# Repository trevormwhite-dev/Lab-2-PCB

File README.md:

# Suggested Changes on Issues Tab
# Check them off if/when they are fixed

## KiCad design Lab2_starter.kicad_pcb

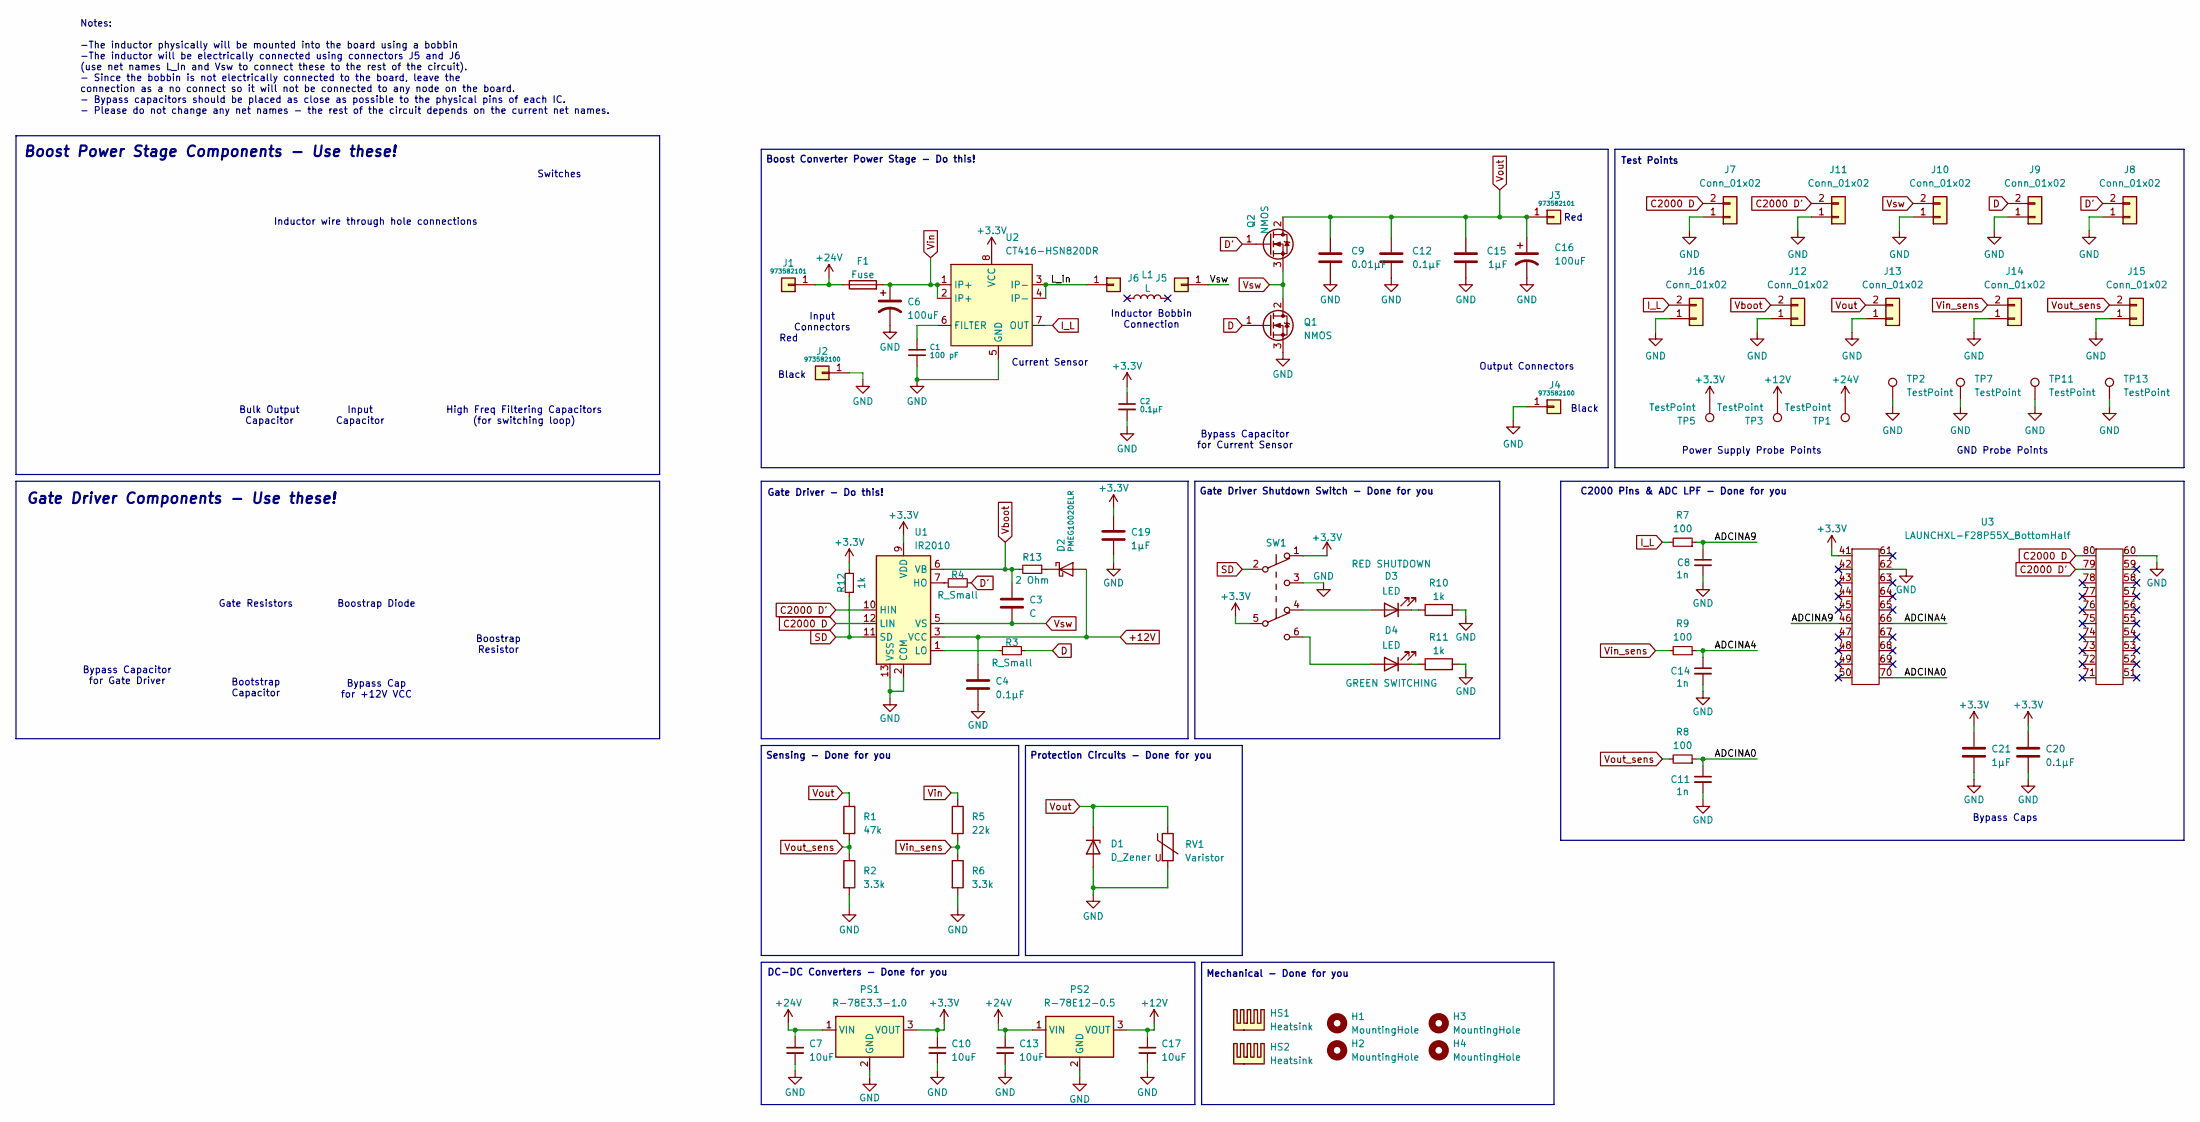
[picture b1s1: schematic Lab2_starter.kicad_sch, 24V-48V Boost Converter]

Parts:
C1: 100 pF; C_0805_2012Metric
C2, C4, C12, C20: 0.1μF; C_0805_2012Metric
C3: C; C_0805_2012Metric
C6, C16: 100uF; 16PX2200MEFC10X20
C7, C10, C13, C17: 10uF; C_0805_2012Metric
C8, C11, C14: 1n; C_0805_2012Metric
C9: 0.01μF; C_0805_2012Metric
C15, C19, C21: 1μF; C_0805_2012Metric
D1: D_Zener; 1.5KE75A
D2: PMEG10020ELR; Nexperia_CFP3_SOD-123W
D3, D4: LED; WL-SMRW_1206_REC
F1: Fuse; 696108003002
H1, H2, H3, H4: MountingHole; MountingHole_3.2mm_M3
HS1, HS2: Heatsink; HSS-B20-NPR-02
J1, J3: 973582101
J2, J4: 973582100
J5, J6: Conn_01x01; Inductor_wire_conn
J7, J8, J9, J10, J11, J12, J13, J14, J15, J16: Conn_01x02; TP
L1: L; Inductor
PS1: R-78E3.3-1.0; PARTREV 6
PS2: R-78E12-0.5; R-78E-0.5_RCP
Q1, Q2: NMOS; TO-220-3_Vertical
R1: 47k; R_0805_2012Metric
R2, R6: 3.3k; R_0805_2012Metric
R3, R4: R_Small; R_0805_2012Metric
R5: 22k; R_0805_2012Metric
R7, R8, R9: 100; R_0805_2012Metric
R10, R11, R12: 1k; R_0805_2012Metric
R13: 2 Ohm; R_0805_2012Metric
RV1: Varistor; V100ZA15P
SW1: SW_Push_DPDT; SLW1116297AD
TP1, TP2, TP3, TP5, TP7, TP11, TP13: TestPoint; TestPoint_Loop_D1.80mm_Drill1.0mm_Beaded
U1: IR2010; 1-2199298-3
U2: CT416-HSN820DR; SOIC-8_3.9x4.9mm_P1.27mm
U3: LAUNCHXL-F28P55X_BottomHalf

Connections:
+3.3V: C2.1, C10.1, C19.1, C20.1, C21.1, PS1.3 (VOUT), R12.2, SW1.1 (A), SW1.5 (B), TP5.1, U1.9 (VDD), U2.8 (VCC), U3.41
+12V: C4.1, C17.1, D2.2 (A), PS2.3 (VOUT), TP3.1, U1.3 (VCC)
+24V: C7.1, C13.1, F1.1, J1.1, PS1.1 (VIN), PS2.1 (VIN), TP1.1
/ADCINA0: C11.1, R8.1, U3.70
/ADCINA4: C14.1, R9.1, U3.66
/ADCINA9: C8.1, R7.1, U3.46
/L_in: J6.1, U2.3 (IP-), U2.4 (IP-)
C2000 D: J7.2, U1.12 (LIN), U3.80
C2000 D': J11.2, U1.10 (HIN), U3.79
D: J9.2, Q1.1 (G), R3.2
D': J8.2, Q2.1 (G), R4.2
I_L: J16.2, R7.2, U2.7 (OUT)
unnamed: D2.1 (K), R13.1
unnamed: D3.2 (A), SW1.4 (A)
unnamed: D3.1 (K), R10.1
unnamed: D4.2 (A), SW1.6 (C)
unnamed: D4.1 (K), R11.1
unnamed: R4.1, U1.7 (HO)
unnamed: R3.1, U1.1 (LO)
unnamed: C1.1, U2.6 (FILTER)
SD: R12.1, SW1.2 (B), U1.11 (SD); also elsewhere on the board
Vboot: C3.1, J12.2, R13.2, U1.6 (VB)
Vin: C6.1, F1.2, R5.1, U2.1 (IP+), U2.2 (IP+)
Vin_sens: J14.2, R5.2, R6.1, R9.2
Vout: C9.1, C12.1, C15.1, C16.1, D1.1 (K), J3.1, J13.2, Q2.2 (D), R1.1, RV1.1
Vout_sens: J15.2, R1.2, R2.1, R8.2
Vsw: C3.2, J5.1, J10.2, Q1.2 (D), Q2.3 (S), U1.5 (VS)

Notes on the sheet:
High Freq Filtering Capacitors (for switching loop)
Inductor wire through hole connections
Input Connectors
Sensing - Done for you
Protection Circuits - Done for you
Input Capacitor
Test Points
Bypass Cap for +12V VCC
Black
Mechanical - Done for you
Red
Bulk Output Capacitor
Power Supply Probe Points
Bootstrap Capacitor
Gate Driver Shutdown Switch - Done for you
Notes: -The inductor physically will be mounted into the board using a bobbin -The inductor will be electrically connected using connectors J5 and J6 (use net names L_In and Vsw to connect these to the rest of the circuit). - Since the bobbin is not electrically connected to the board, leave the co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
Gate Driver - Do this!
Current Sensor
Boostrap Resistor
DC-DC Converters - Done for you
Boost Power Stage Components - Use these!
Gate Resistors
C2000 Pins & ADC LPF - Done for you
Boostrap Diode
Output Connectors
Bypass Capacitor for Current Sensor
Inductor Bobbin Connection
Switches
Bypass Capacitor for Gate Driver
Gate Driver Components - Use these!
GND Probe Points
Bypass Caps
Boost Converter Power Stage - Do this!

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
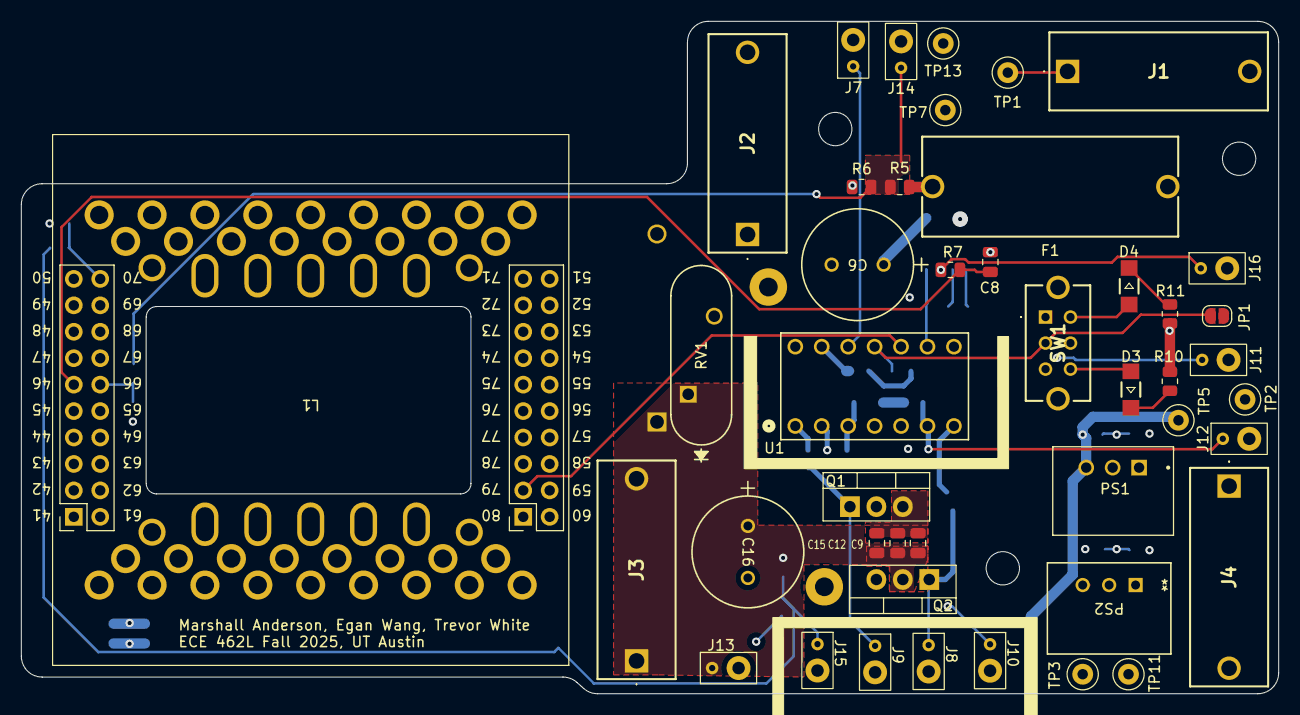
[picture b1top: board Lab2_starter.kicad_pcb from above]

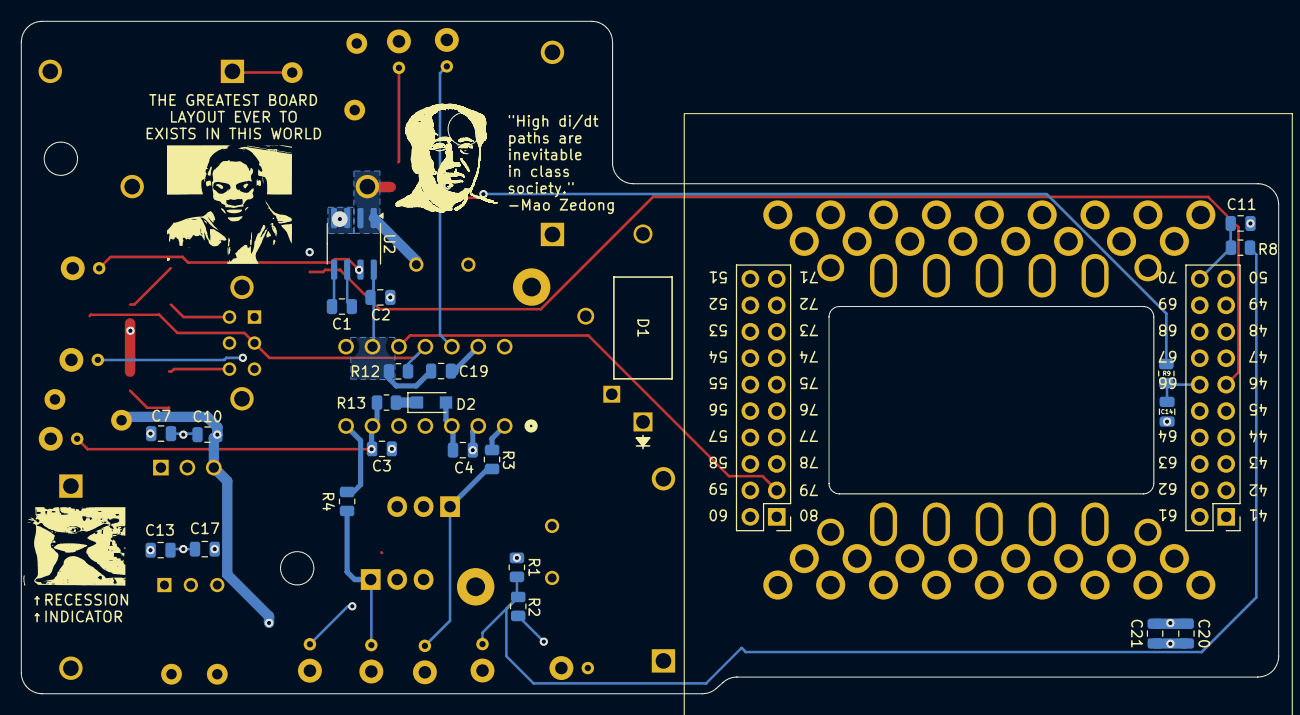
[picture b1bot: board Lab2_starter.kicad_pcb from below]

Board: 4 copper layers, 120.8 x 64.6 mm, 77 parts (25 on the bottom side), 29 nets.

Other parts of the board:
JP1: SolderJumper_2_Open; SolderJumper-2_P1.3mm_Open_RoundedPad1.0x1.5mm

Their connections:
SD: JP1.2 (B); also elsewhere on the board

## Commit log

2025-09-30 Added whole project instead of just pcb file
2025-09-30 fresh restart I suppose
2025-09-30 Added just files not including autosaves, will see if can remove autosaves separately
2025-09-30 Deleted autosave files
2025-09-30 Moved decoupling RC filters next to C2000 IO pins
2025-10-03 updated PCB annulus, changed ADC traces
2025-10-03 edited Mao quote spacing, further reduced board size
2025-10-03 shrunk driver loop, moved ADC sensing to be shorter - need to ask about hi dv/dt overlaying ground plane + low side decoupling cap
2025-10-03 further reduced board size, reworked V_sw node as trace instead of pour, moved V_out pour to front layer and thickened
2025-10-03 added elon inflation
2025-10-03 Fixed DRC errors and reduced board size (again)
2025-11-02 started work on bidirectional voltage converter topology

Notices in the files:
parts and their libraries:
Copyright 2016 Accelerated Designs. All rights reserved.
